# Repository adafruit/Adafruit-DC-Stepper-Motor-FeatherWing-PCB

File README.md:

## Adafruit DC Stepper Motor FeatherWing PCB
<a href="http://www.adafruit.com/products/2927"><br/>
Click here to purchase one from the Adafruit shop</a>

This is the DC Motor + Stepper FeatherWing which will let you use 2 x bi-polar stepper motors or 4 x brushed DC motors (or 1 stepper and 2 DC motors). Using our Feather Stacking Headers or Feather Female Headers you can connect a FeatherWing on top or bottom of your Feather board and let the board take flight!

The original Adafruit Motorshield Kit is one of our most beloved kits, which is why we decided to squish it all together on a FeatherWing to make something even smaller, lighter, and more portable! Instead of using a latch and the Arduino's PWM pins, we have a fully-dedicated PWM driver chip onboard. This chip handles all the motor and speed controls over I2C.

PCB files for Adafruit DC Stepper Motor FeatherWing. The format is EagleCAD schematic and board layout
- https://www.adafruit.com/products/2927

### License

Adafruit invests time and resources providing this open source design, please support Adafruit and open-source hardware by purchasing products from [Adafruit](https://www.adafruit.com)!

All text above must be included in any redistribution

Designed by Limor Fried/Ladyada for Adafruit Industries.
Creative Commons Attribution/Share-Alike, all text above must be included in any redistribution. 
See license.txt for additional information.

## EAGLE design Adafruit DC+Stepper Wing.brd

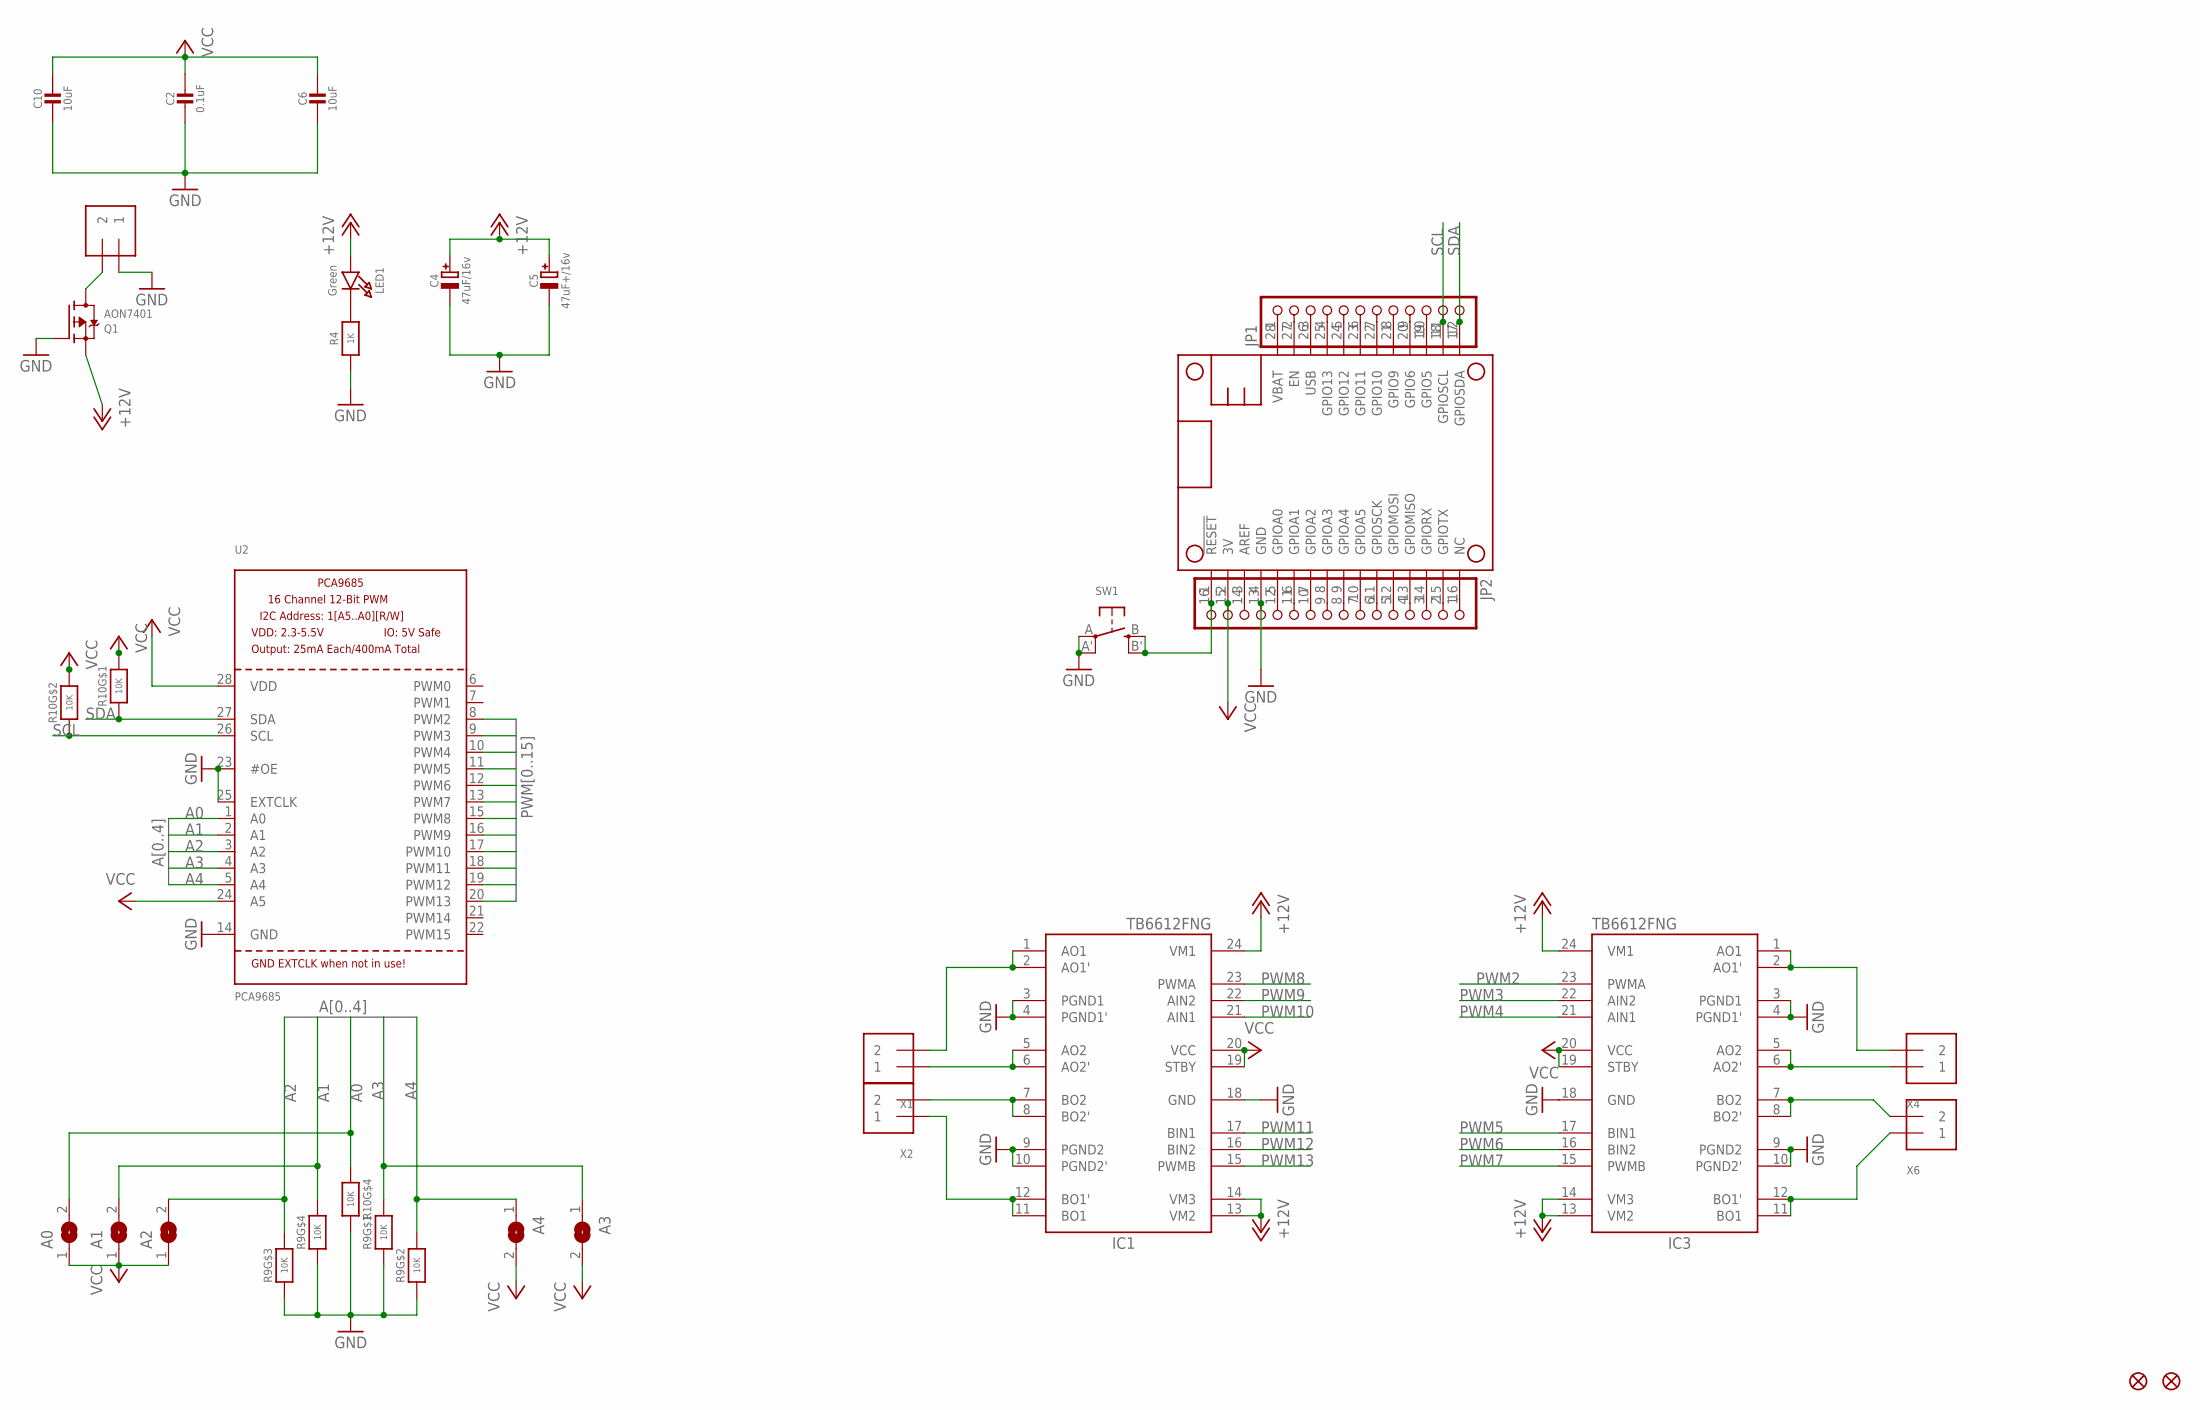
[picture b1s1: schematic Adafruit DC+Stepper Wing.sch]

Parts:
A0, A1, A2, A3, A4: SOLDERJUMPERREFLOW_NOPASTE; SOLDERJUMPER_REFLOW_NOPASTE
C2: 0.1uF; 0805-NO
C4: 47uF/16v; PANASONIC_C
C5: 47uF+/16v; PANASONIC_C
C6, C10: 10uF; 0805-NO
IC1, IC3: TB6612FNG; SSOP24
JP1: HEADER-1X12; 1X12_ROUND
JP2: HEADER-1X16ROUND; 1X16_ROUND
LED1: Green; CHIPLED_0805_NOOUTLINE
MPOWER: 1X2-3.5MM
MS1: FEATHERWING
Q1: AON7401; POWERDI3333
R4: 1K; 0805-NO
R9, R10: 10K; RESPACK_4X0603
SW1: SWITCH_TACT_SMT4.6X2.8; BTN_KMR2_4.6X2.8
U2: PCA9685; TSSOP28
U$3, U$4: FIDUCIAL""; FIDUCIAL_1MM
X1, X2, X4, X6: TERMBLOCK_1X2; TERMBLOCK_1X2-3.5MM

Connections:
+12V: C4.+, C5.+, IC1.13 (VM2), IC1.14 (VM3), IC1.24 (VM1), IC3.13 (VM2), IC3.14 (VM3), IC3.24 (VM1), LED1.A, Q1.1 (S), Q1.2 (S), Q1.3 (S)
A0: A0.2, R10.4 (1), U2.1 (A0)
A1: A1.2, R9.5 (2), U2.2 (A1)
A2: A2.2, R9.6 (2), U2.3 (A2)
A3: A3.1, R9.8 (2), U2.4 (A3)
A4: A4.1, R9.7 (2), U2.5 (A4)
GND: C2.2, C4.-, C5.-, C6.2, C10.2, IC1.3 (PGND1), IC1.4 (PGND1'), IC1.9 (PGND2), IC1.10 (PGND2'), IC1.18 (GND), IC3.3 (PGND1), IC3.4 (PGND1'), IC3.9 (PGND2), IC3.10 (PGND2'), IC3.18 (GND), JP2.13, MPOWER.1, MS1.4 (GND), Q1.4 (G), R4.1, R9.1, R9.2 (1), R9.3 (1), R9.4 (1), R10.5 (2), SW1.A, SW1.A' (P1), U2.14 (GND), U2.23 (#OE), U2.25 (EXTCLK)
unnamed: JP1.2, MS1.27 (EN)
unnamed: JP1.4, MS1.25 (GPIO13)
unnamed: MPOWER.2, Q1.5678 (D)
unnamed: IC1.1 (AO1), IC1.2 (AO1'), X1.2
unnamed: JP1.5, MS1.24 (GPIO12)
unnamed: IC1.5 (AO2), IC1.6 (AO2'), X1.1
unnamed: IC1.7 (BO2), IC1.8 (BO2'), X2.2
unnamed: JP1.6, MS1.23 (GPIO11)
unnamed: IC1.11 (BO1), IC1.12 (BO1'), X2.1
unnamed: JP1.7, MS1.22 (GPIO10)
unnamed: JP1.8, MS1.21 (GPIO9)
unnamed: IC3.1 (AO1), IC3.2 (AO1'), X4.2
unnamed: JP1.9, MS1.20 (GPIO6)
unnamed: IC3.5 (AO2), IC3.6 (AO2'), X4.1
unnamed: IC3.7 (BO2), IC3.8 (BO2'), X6.2
unnamed: JP1.10, MS1.19 (GPIO5)
unnamed: IC3.11 (BO1), IC3.12 (BO1'), X6.1
unnamed: JP2.1, MS1.16 (NC)
unnamed: JP2.2, MS1.15 (GPIOTX)
unnamed: JP2.3, MS1.14 (GPIORX)
unnamed: JP2.4, MS1.13 (GPIOMISO)
unnamed: JP2.5, MS1.12 (GPIOMOSI)
unnamed: JP2.6, MS1.11 (GPIOSCK)
unnamed: JP2.7, MS1.10 (GPIOA5)
unnamed: JP2.8, MS1.9 (GPIOA4)
unnamed: JP2.9, MS1.8 (GPIOA3)
unnamed: JP2.10, MS1.7 (GPIOA2)
unnamed: JP2.11, MS1.6 (GPIOA1)
unnamed: JP2.12, MS1.5 (GPIOA0)
unnamed: JP2.14, MS1.3 (AREF)
unnamed: JP2.16, MS1.1 (!RESET), SW1.B (S), SW1.B' (S1)
unnamed: LED1.C, R4.2
PWM2: IC3.23 (PWMA), U2.8 (PWM2)
PWM3: IC3.22 (AIN2), U2.9 (PWM3)
PWM4: IC3.21 (AIN1), U2.10 (PWM4)
PWM5: IC3.17 (BIN1), U2.11 (PWM5)
PWM6: IC3.16 (BIN2), U2.12 (PWM6)
PWM7: IC3.15 (PWMB), U2.13 (PWM7)
PWM8: IC1.23 (PWMA), U2.15 (PWM8)
PWM9: IC1.22 (AIN2), U2.16 (PWM9)
PWM10: IC1.21 (AIN1), U2.17 (PWM10)
PWM11: IC1.17 (BIN1), U2.18 (PWM11)
PWM12: IC1.16 (BIN2), U2.19 (PWM12)
PWM13: IC1.15 (PWMB), U2.20 (PWM13)
SCL: JP1.11, MS1.18 (GPIOSCL), R10.2 (1), U2.26 (SCL)
SDA: JP1.12, MS1.17 (GPIOSDA), R10.1, U2.27 (SDA)
USB: JP1.3, MS1.26 (USB)
VBAT: JP1.1, MS1.28 (VBAT)
VCC: A0.1, A1.1, A2.1, A3.2, A4.2, C2.1, C6.1, C10.1, IC1.19 (STBY), IC1.20 (VCC), IC3.19 (STBY), IC3.20 (VCC), JP2.15, MS1.2 (3V), R10.7 (2), R10.8 (2), U2.24 (A5), U2.28 (VDD)

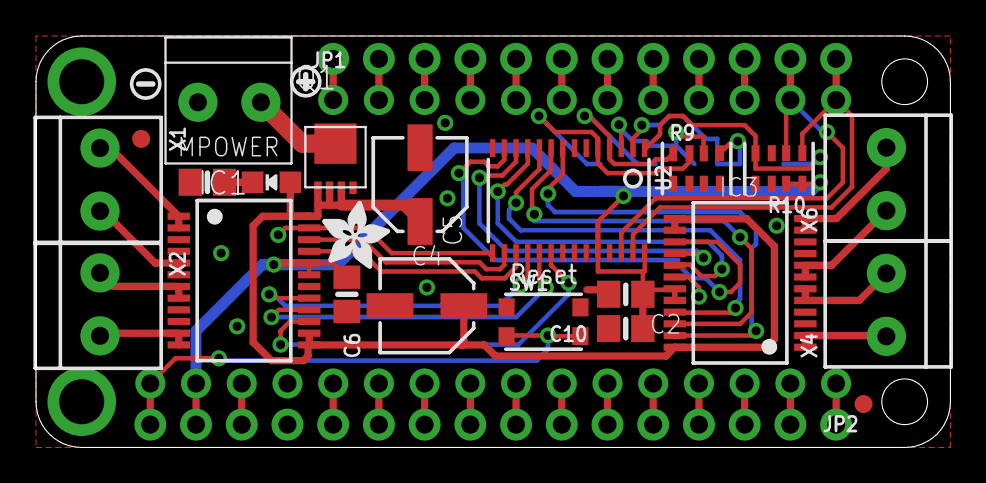
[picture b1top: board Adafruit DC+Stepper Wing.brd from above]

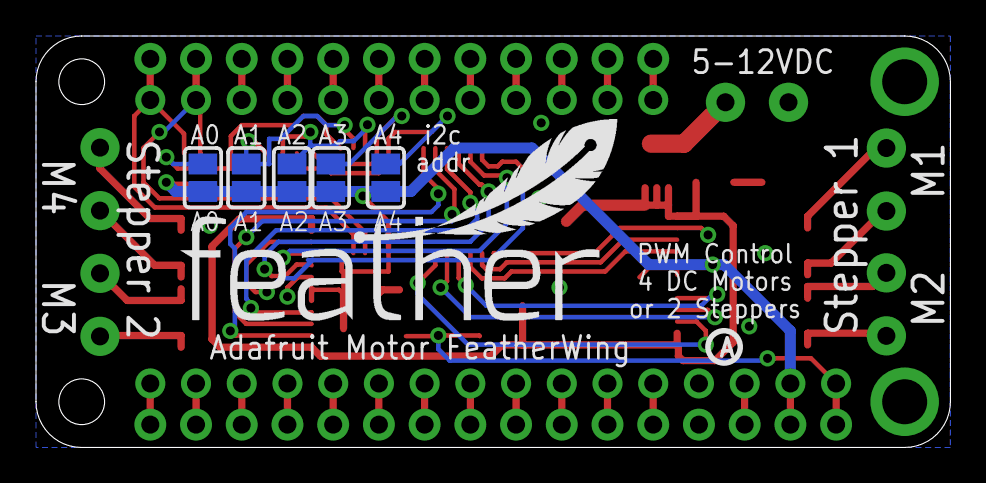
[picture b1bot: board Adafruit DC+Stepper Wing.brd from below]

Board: 2 copper layers, 50.8 x 22.9 mm, 34 parts (7 on the bottom side), 56 nets.

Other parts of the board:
U$1: SYMBOL_PLUS
U$2: SYMBOL_MINUS
U$5: ADAFRUIT_3.5MM
U$6: FEATHERLOGO
U$8: PCBFEAT-REV-040

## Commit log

2016-03-01 init

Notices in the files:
parts and their libraries:
microbuilder: This work is placed in the public domain, and may be freely used for commercial and non-commercial work with the following conditions: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
